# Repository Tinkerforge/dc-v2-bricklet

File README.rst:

DC Bricklet 2.0
===============

This repository contains the firmware source code and the hardware design
files. The documentation generator configs can be found at
https://github.com/Tinkerforge/generators

Repository Content
------------------

software/:
 * examples/: Examples for all supported languages
 * build/: Compiled files
 * src/: Source code of firmware
 * Makefile: Makefile to build project

hardware/:
 * Contains KiCad project files and additionally schematics as PDF

datasheets/:
 * Contains datasheets for sensors and complex ICs that are used

Hardware
--------

The hardware is designed with the open source EDA Suite KiCad
(http://www.kicad.org). Before you are able to open the files,
you have to install the Tinkerforge kicad-libraries
(https://github.com/Tinkerforge/kicad-libraries). You can either clone
them directly in hardware/ or clone them in a separate folder and
symlink them into hardware/
(ln -s kicad_path/kicad-libraries project_path/hardware). After that you
can open the .pro file in hardware/ with KiCad and from there view and
modify the schematics and the PCB layout.

Software
--------

If you want to do your own Brick/Bricklet firmware development we highly
recommend that you use our build environment setup script and read the
tutorial (https://www.tinkerforge.com/en/doc/Tutorials/Tutorial_Build_Environment/Tutorial.html).

To compile the C code we recommend you to install the newest GNU Arm Embedded
Toolchain (https://launchpad.net/gcc-arm-embedded/+download).
You also need to install bricklib2 (https://github.com/Tinkerforge/bricklib2).

You can either clone it directly in software/src/ or clone it in a
separate folder and symlink it into software/src/
(ln -s bricklib_path/bricklib2 project_path/software/src/). Finally make sure to
have CMake installed (http://www.cmake.org/cmake/resources/software.html).

After that you can build the firmware by invoking make in software/.
The firmware (.zbin) can then be found in software/build/ and uploaded
with brickv (click button "Flashing" on start screen).

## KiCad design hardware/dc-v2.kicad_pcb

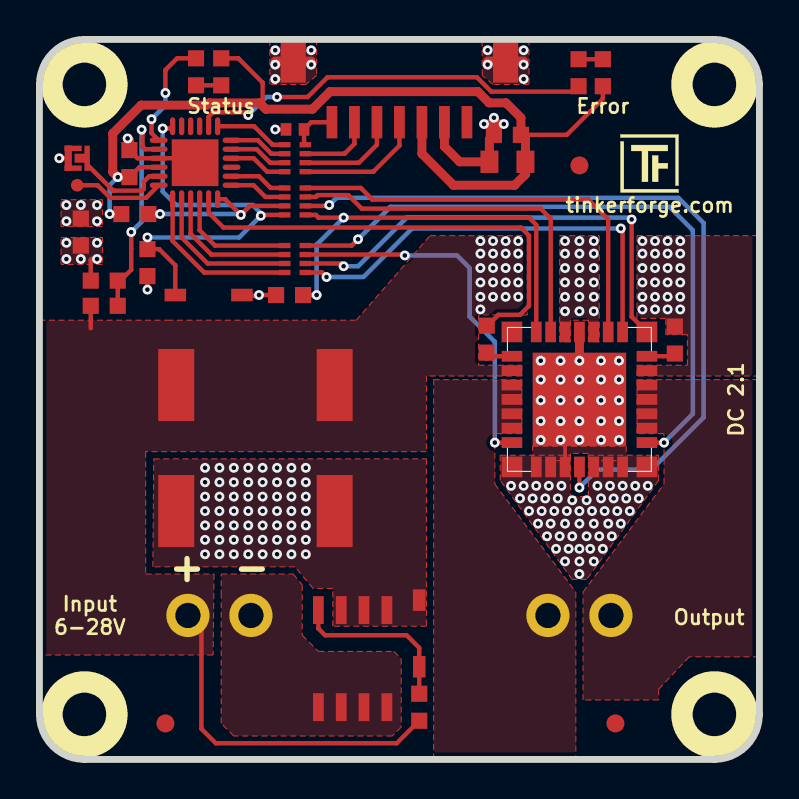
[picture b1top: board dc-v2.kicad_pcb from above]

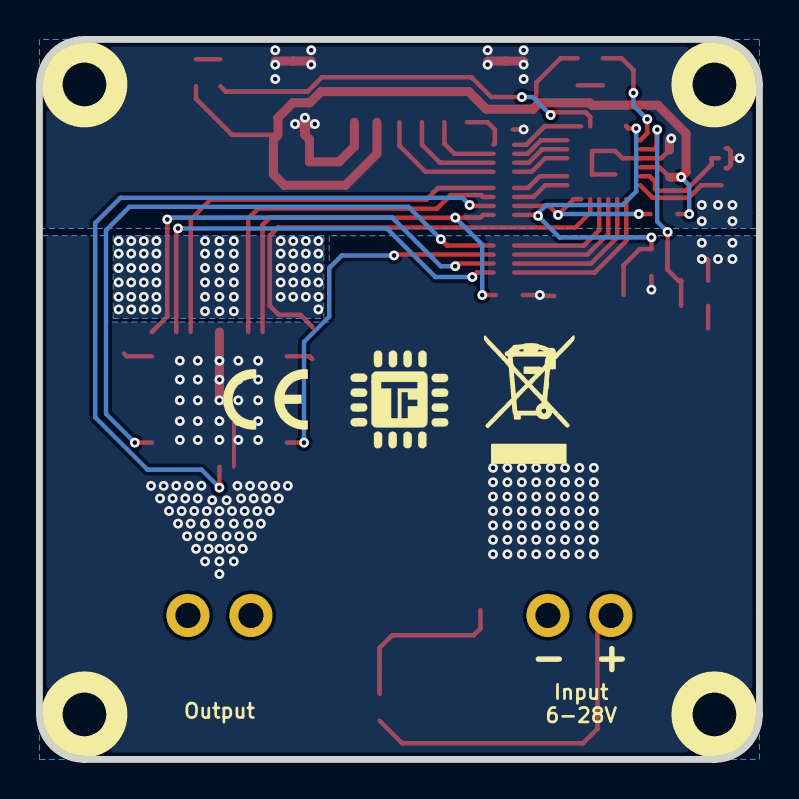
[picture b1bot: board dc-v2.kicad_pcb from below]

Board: 2 copper layers, 40.0 x 40.0 mm, 41 parts (2 on the bottom side), 42 nets.

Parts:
C1: 470nF; C0603F
C2, C4: 220µF/35V; ELKO_83
C3, C104: 100nF; C0603F
C101: 10uF; C0805
C102: 220pF; C0402F
C103: 1uF; C0603F
D1: Z3.3V; SOD-123
D2: Z12V; SOD-123
D3: red; D0603F
D101: blue; D0603F
Fiducial_Mark: VAL**; Fiducial_Mark
Fiducial_Mark#2, Fiducial_Mark#3: VAL**; Fiducial_Mark
L1: FB; 0603F
P1: black; OQ_2P
P2: green; OQ_2P
P101: CON-SENSOR2
P102: DEBUG; DEBUG_PAD
P103: BOOT; SolderJumper
Q1: FDS8449; SOIC-8-MOSFET
R1, R4, R7, R101: 1k; R0603F
R2: 220; R0603F
R3, R6: 10k; R0603F
R5: 100k; R0603F
RP1, RP2: 1k; 4X0402
RP101: 82; 4X0402
U1: MC33926; PQFN-32
U101: XMC1302; QFN24-4x4mm-0.5mm
U103, U104, U105, U106: DRILL; DRILL_NP
VAL: WEEE_7mm
VAL#2: CE_5mm

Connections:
3V3: C101.2, C103.2, C104.1, D3.1, D101.1, P101.3, R6.1, U101.10
AGND: C1.2, C2.2, C4.2, D1.1, D2.1, L1.1, Q1.S, R2.2, R4.2, U1.5, U1.17, U1.18, U1.19, U1.20, U1.22, U1.23, U1.24, U1.25, U1.EP
GND: C101.1, C102.1, C103.1, C104.2, L1.2, P101.2, P101.EP, P103.1, U101.9, U101.EXP
unnamed: C3.2, U1.32
unnamed: C102.2, P101.7, RP101.4
unnamed: D2.2, Q1.G, R5.2
unnamed: D3.2, R7.2
unnamed: D101.2, R101.2
unnamed: P1.2, Q1.D
unnamed: P2.1, U1.12, U1.13, U1.14, U1.15
unnamed: P2.2, U1.27, U1.28, U1.29, U1.30
unnamed: P101.4, RP101.1
unnamed: P101.5, RP101.2
unnamed: P101.6, RP101.3
unnamed: P102.1, U101.12
unnamed: P103.2, U101.11
unnamed: R1.2, U1.10
unnamed: R2.1, RP2.5, U1.8
unnamed: R7.1, U101.2
unnamed: R101.1, U101.7
unnamed: RP1.5, U1.2
unnamed: RP1.6, U1.1
unnamed: RP1.7, U1.16
unnamed: RP1.8, U1.26
unnamed: RP2.6, U1.21
unnamed: RP2.7, U1.7
unnamed: RP2.8, U1.3
PWR-D1: RP1.2, U101.15
PWR-D2: RP1.1, U101.16
PWR-EN: R1.1, U101.17
PWR-FB: C1.1, D1.2, RP2.4, U101.6
PWR-IN1: RP1.4, U101.13
PWR-IN2: RP1.3, U101.14
PWR-INV: RP2.1, U101.20
PWR-SLEW: RP2.2, U101.19
PWR-STATUS: R6.2, RP2.3, U101.18
PWR-VEXT: R3.2, R4.1, U101.8
S-CLK: RP101.7, U101.23
S-CS: RP101.8, U101.22
S-MISO: RP101.5, U101.1
S-MOSI: RP101.6, U101.24
VCC: C2.1, C3.1, C4.1, P1.1, R3.1, R5.1, U1.4, U1.6, U1.11, U1.31

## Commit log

2020-10-06 initial push
2020-10-07 pcb design
2020-10-08 ready for prototype
2020-10-28 prototype
2020-11-20 Add auto-generated firmware stub
2020-11-20 Add DC Bricklet 2.0 firmware implementation
    This is mostly based on the firmware of the Performance DC Bricklet.
2020-11-23 Add Emergency Shutdown callback support
2020-11-23 Rev 2.1 : changed Status LED pin, changed footprint R1 to 0603F, added Via's under MC33926 IC
2021-01-11 specify processor
2021-04-28 3d add heatsink, add schematic
2021-04-28 add license
2021-04-28 fix 3d paths
2021-04-28 add 3d data
2021-05-04 Add examples
2021-05-11 examples: Remove outdated comments
2021-05-27 readme: Remove in-development marker
2021-05-27 Update changelog
2021-10-25 Update KiCad link
    https://www.kicad.org/blog/2021/10/Avoid-links-to-former-kicad-domain/
2022-04-19 examples: uc: Rename TF_HalContext to TF_HAL.
2022-04-26 uc: Adapt to bindings changes
2022-07-06 Add license files.

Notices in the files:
hardware/dc-v2.kicad_pcb:
Licensed under CERN OHL v.1.1
Copyright (©) 2020, T.Schneidermann
Copyright Tinkerforge GmbH 2020.
This documentation describes Open Hardware and is licensed under the
CERN OHL v. 1.1.
